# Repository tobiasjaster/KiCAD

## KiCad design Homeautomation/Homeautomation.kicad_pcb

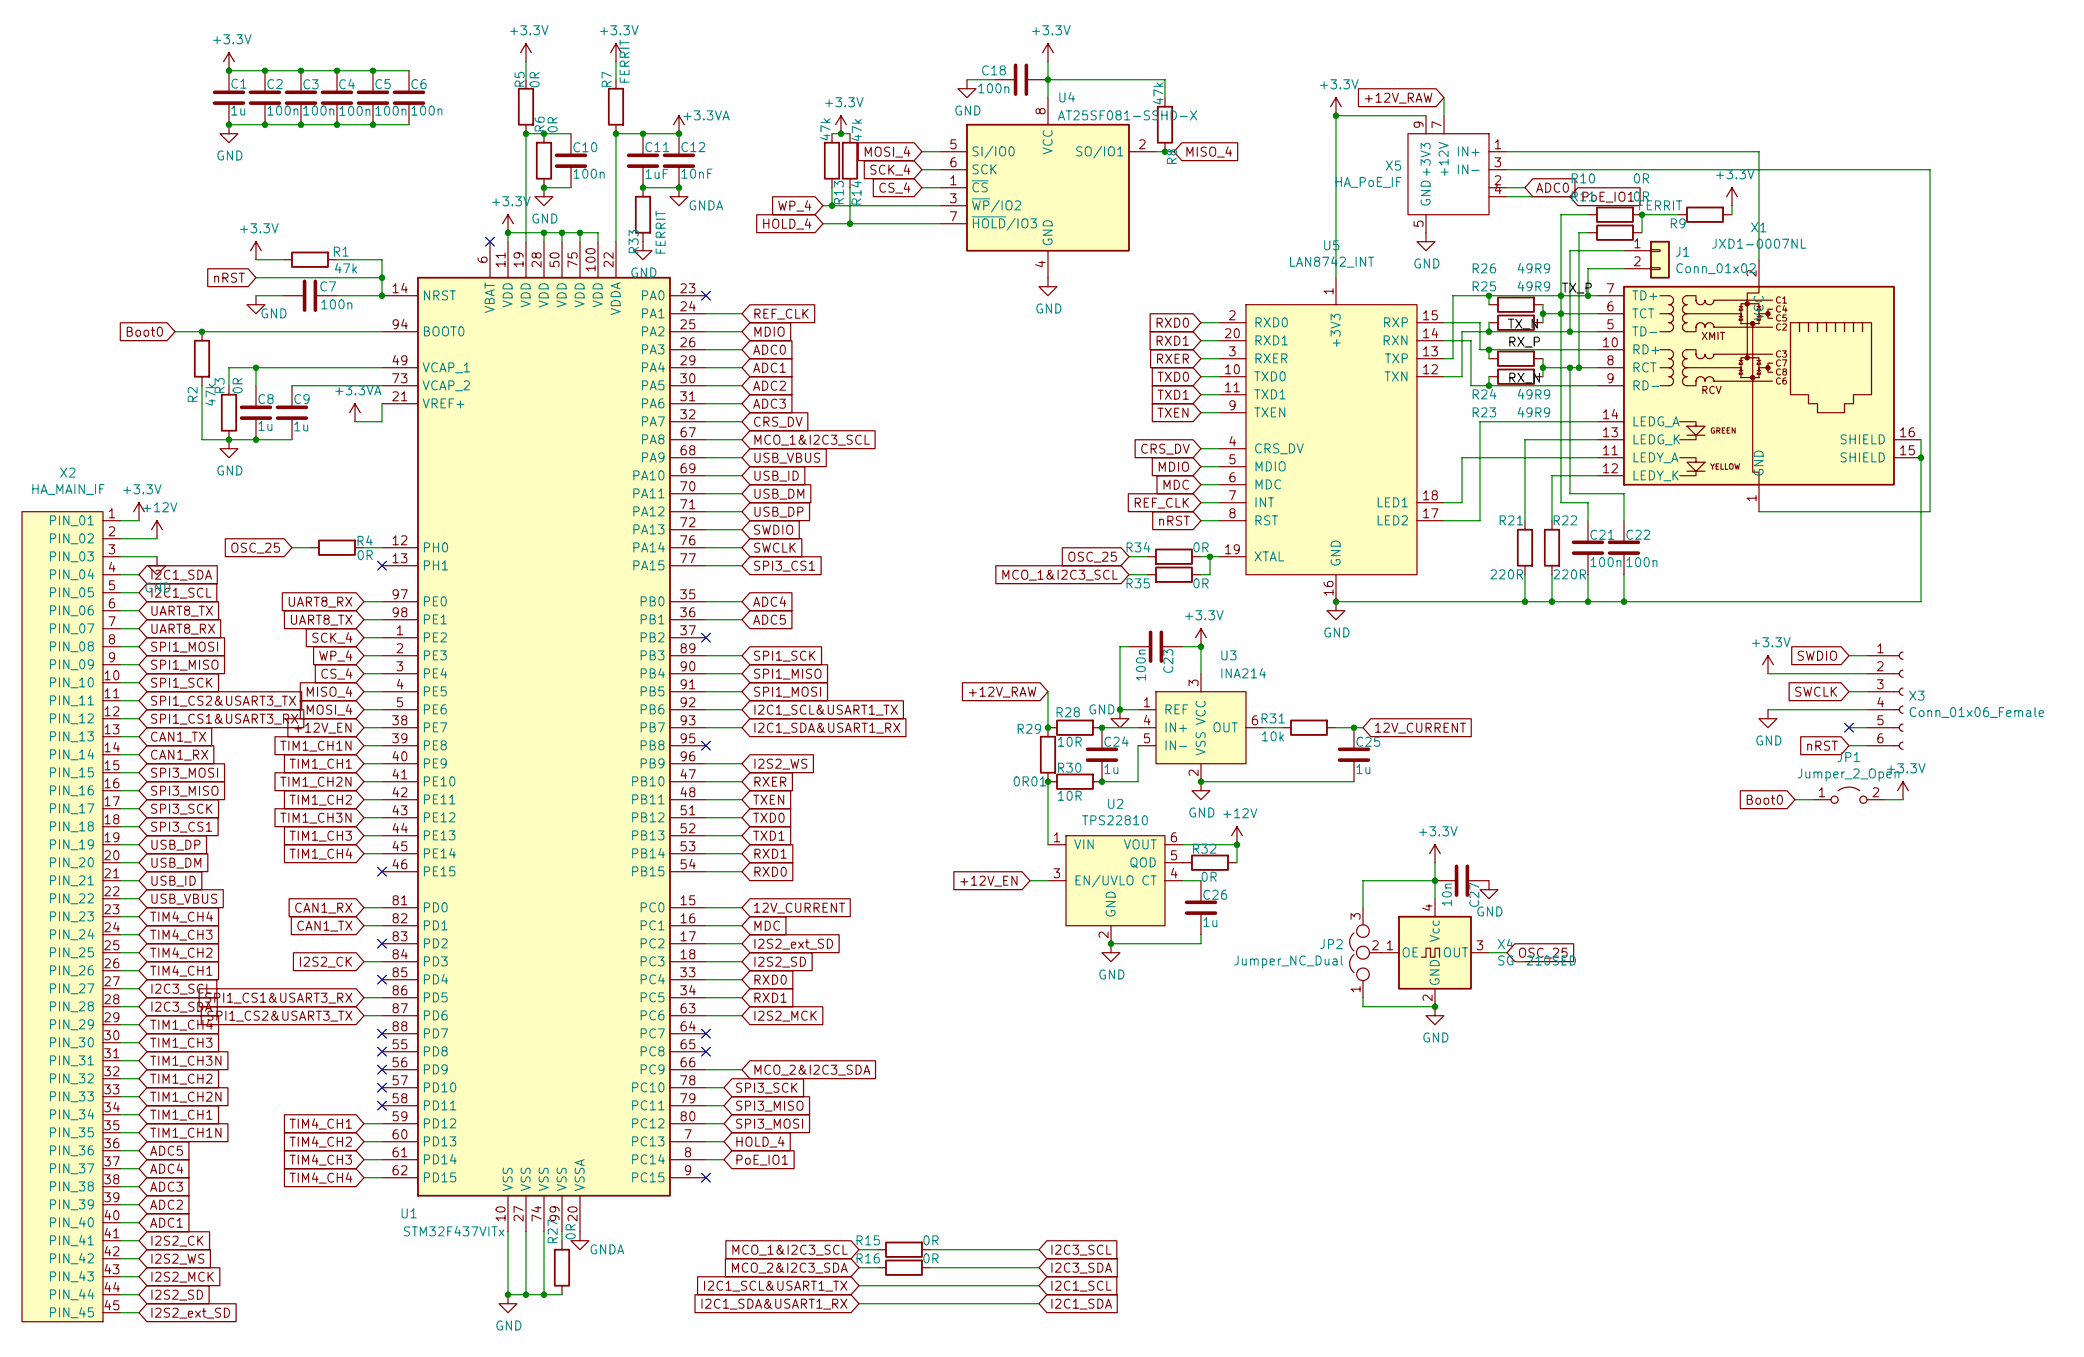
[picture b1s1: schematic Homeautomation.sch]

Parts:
C1, C8, C9, C24, C25, C26: 1u; C_0603_1608Metric
C2, C3, C4, C5, C6, C7, C10, C18, C21, C22, C23: 100n; C_0402_1005Metric
C11: 1uF; C_0603_1608Metric
C12: 10nF; C_0402_1005Metric
C27: 10n; C_0603_1608Metric
J1: Conn_01x02; Wago_243_211_1x02_P5.80mm_Vertical
JP1: Jumper_2_Open; SolderJumper-2_P1.3mm_Open_Pad1.0x1.5mm
JP2: Jumper_NC_Dual; SolderJumper-3_P1.3mm_Open_RoundedPad1.0x1.5mm
R1, R2, R8, R13, R14: 47k; R_0402_1005Metric
R3, R4, R5, R6, R10, R11, R15, R16, R27, R32, R34, R35: 0R; R_0402_1005Metric
R7, R9, R33: FERRIT; R_0603_1608Metric
R21, R22: 220R; R_0402_1005Metric
R23, R24, R25, R26: 49R9; R_0402_1005Metric
R28, R30: 10R; R_0402_1005Metric
R29: 0R01; R_0805_2012Metric
R31: 10k; R_0402_1005Metric
U1: STM32F437VITx; LQFP-100_14x14mm_P0.5mm
U2: TPS22810; SOT-23-6
U3: INA214; SOT-363_SC-70-6
U4: AT25SF081-SSHD-X; SOIC-8_3.9x4.9mm_P1.27mm
U5: LAN8742_INT; Bus_Interface_TJHome_Base
X1: JXD1-0007NL
X2: HA_MAIN_IF; HA_MAIN_IF2
X3: Conn_01x06_Female; JST_SH_SM06B-SRSS-TB_1x06-1MP_P1.00mm_Horizontal
X4: SG-210SED; Oscillator_SMD_SeikoEpson_SG210-4Pin_2.5x2.0mm
X5: HA_PoE_IF

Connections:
12V_CURRENT: C25.2, R31.2, U1.15 (PC0)
+3.3VA: C11.1, C12.1, R7.2, U1.21 (VREF+), U1.22 (VDDA)
+3V3: C1.1, C2.1, C3.1, C4.1, C5.1, C6.1, C18.1, C23.2, C27.1, JP1.2 (B), JP2.3, R1.1, R5.1, R7.1, R8.2, R9.2, R13.2, R14.2, U1.11 (VDD), U1.28 (VDD), U1.50 (VDD), U1.75 (VDD), U1.100 (VDD), U3.3 (VCC), U4.8 (VCC), U5.1 (+3V3), X2.1 (PIN_01), X3.2, X4.4 (Vcc), X5.9 (+3V3), X5.10; also elsewhere on the board
+12V: R32.2, U2.6 (VOUT), X2.2 (PIN_02)
+12V_EN: U1.38 (PE7), U2.3 (EN/UVLO)
+12V_RAW: R28.1, R29.1, X5.7 (+12V), X5.8
/RX_N: R23.1, U5.14 (RXN), X1.9 (RD-)
/RX_P: R24.1, U5.15 (RXP), X1.10 (RD+)
/TX_N: J1.1, R25.1, U5.12 (TXN), X1.5 (TD-)
/TX_P: C21.2, J1.2, R10.1, R25.2, R26.1, R26.2, U5.13 (TXP), X1.6 (TCT), X1.7 (TD+)
ADC0: U1.26 (PA3), X5.2
ADC1: U1.29 (PA4), X2.40 (PIN_40)
ADC2: U1.30 (PA5), X2.39 (PIN_39)
ADC3: U1.31 (PA6), X2.38 (PIN_38)
ADC4: U1.35 (PB0), X2.37 (PIN_37)
ADC5: U1.36 (PB1), X2.36 (PIN_36)
Boot0: JP1.1 (A), R2.1, U1.94 (BOOT0)
CAN1_RX: U1.81 (PD0), X2.14 (PIN_14)
CAN1_TX: U1.82 (PD1), X2.13 (PIN_13)
CRS_DV: U1.32 (PA7), U5.4 (CRS_DV)
CS_4: U1.3 (PE4), U4.1 (~CS)
GND: C1.2, C2.2, C3.2, C4.2, C5.2, C6.2, C7.2, C8.2, C9.2, C10.2, C18.2, C21.1, C22.1, C23.1, C25.1, C26.1, C27.2, JP2.1, R2.2, R3.1, R6.1, R21.2, R22.2, R27.1, R33.2, U1.10 (VSS), U1.27 (VSS), U1.74 (VSS), U2.2 (GND), U3.1 (REF), U3.2 (VSS), U4.4 (GND), U5.16 (GND), X1.15 (SHIELD), X1.16 (SHIELD), X2.3 (PIN_03), X3.4, X4.2 (GND), X5.5 (GND), X5.6 (GND)
GNDA: C11.2, C12.2, R33.1, U1.20 (VSSA)
HOLD_4: R14.1, U1.7 (PC13), U4.7 (~HOLD~/IO3)
I2C1_SCL: U1.92 (PB6), X2.5 (PIN_05); also elsewhere on the board
I2C1_SDA: U1.93 (PB7), X2.4 (PIN_04); also elsewhere on the board
I2C3_SCL: R15.2, X2.27 (PIN_27); also elsewhere on the board
I2C3_SDA: R16.2, X2.28 (PIN_28); also elsewhere on the board
I2S2_CK: U1.84 (PD3), X2.41 (PIN_41)
I2S2_MCK: U1.63 (PC6), X2.43 (PIN_43)
I2S2_SD: U1.18 (PC3), X2.44 (PIN_44)
I2S2_WS: U1.96 (PB9), X2.42 (PIN_42)
I2S2_ext_SD: U1.17 (PC2), X2.45 (PIN_45)
MCO_1&I2C3_SCL: R15.1, R35.2, U1.67 (PA8)
MCO_2&I2C3_SDA: R16.1, U1.66 (PC9)
MDC: U1.16 (PC1), U5.6 (MDC)
MDIO: U1.25 (PA2), U5.5 (MDIO)
MISO_4: R8.1, U1.4 (PE5), U4.2 (SO/IO1)
MOSI_4: U1.5 (PE6), U4.5 (SI/IO0)
unnamed: C8.1, R3.2, U1.49 (VCAP_1)
unnamed: C9.1, U1.73 (VCAP_2)
unnamed: C10.1, R5.2, R6.2, U1.19 (VDD)
unnamed: C22.2, R11.1, R23.2, R24.2, X1.8 (RCT)
unnamed: C24.1, R30.2, U3.5 (IN-)
unnamed: C24.2, R28.2, U3.4 (IN+)
unnamed: C26.2, U2.4 (CT)
unnamed: JP2.2, X4.1 (OE)
unnamed: R4.2, U1.12 (PH0)
unnamed: R9.1, R10.2, R11.2
unnamed: R21.1, X1.13 (LEDG_K)
unnamed: R22.1, X1.12 (LEDY_K)
unnamed: R27.2, U1.99 (VSS)
unnamed: R29.2, R30.1, U2.1 (VIN)
unnamed: R31.1, U3.6 (OUT)
unnamed: R32.1, U2.5 (QOD)
unnamed: R34.1, R35.1, U5.19 (XTAL)
unnamed: U5.17 (LED2), X1.14 (LEDG_A)
unnamed: U5.18 (LED1), X1.11 (LEDY_A)
unnamed: X1.1 (GND), X5.3 (IN-)
unnamed: X1.2 (VCC), X5.1 (IN+)
OSC_25: R4.1, R34.2, X4.3 (OUT)
PoE_IO1: U1.8 (PC14), X5.4
REF_CLK: U1.24 (PA1), U5.7 (INT)
RXD0: U1.33 (PC4), U1.54 (PB15), U5.2 (RXD0)
RXD1: U1.34 (PC5), U1.53 (PB14), U5.20 (RXD1)
RXER: U1.47 (PB10), U5.3 (RXER)
SCK_4: U1.1 (PE2), U4.6 (SCK)
SPI1_CS1&USART3_RX: U1.86 (PD5), X2.12 (PIN_12)
SPI1_CS2&USART3_TX: U1.87 (PD6), X2.11 (PIN_11)
SPI1_MISO: U1.90 (PB4), X2.9 (PIN_09)
SPI1_MOSI: U1.91 (PB5), X2.8 (PIN_08)
SPI1_SCK: U1.89 (PB3), X2.10 (PIN_10)
SPI3_CS1: U1.77 (PA15), X2.18 (PIN_18)
SPI3_MISO: U1.79 (PC11), X2.16 (PIN_16)
SPI3_MOSI: U1.80 (PC12), X2.15 (PIN_15)
SPI3_SCK: U1.78 (PC10), X2.17 (PIN_17)
SWCLK: U1.76 (PA14), X3.3
SWDIO: U1.72 (PA13), X3.1
TIM1_CH1: U1.40 (PE9), X2.34 (PIN_34)
TIM1_CH1N: U1.39 (PE8), X2.35 (PIN_35)
TIM1_CH2: U1.42 (PE11), X2.32 (PIN_32)
TIM1_CH2N: U1.41 (PE10), X2.33 (PIN_33)
TIM1_CH3: U1.44 (PE13), X2.30 (PIN_30)
TIM1_CH3N: U1.43 (PE12), X2.31 (PIN_31)
TIM1_CH4: U1.45 (PE14), X2.29 (PIN_29)
TIM4_CH1: U1.59 (PD12), X2.26 (PIN_26)
TIM4_CH2: U1.60 (PD13), X2.25 (PIN_25)
TIM4_CH3: U1.61 (PD14), X2.24 (PIN_24)
TIM4_CH4: U1.62 (PD15), X2.23 (PIN_23)
TXD0: U1.51 (PB12), U5.10 (TXD0)
TXD1: U1.52 (PB13), U5.11 (TXD1)
TXEN: U1.48 (PB11), U5.9 (TXEN)
UART8_RX: U1.97 (PE0), X2.7 (PIN_07)
UART8_TX: U1.98 (PE1), X2.6 (PIN_06)
USB_DM: U1.70 (PA11), X2.20 (PIN_20)
USB_DP: U1.71 (PA12), X2.19 (PIN_19)
USB_ID: U1.69 (PA10), X2.21 (PIN_21)
USB_VBUS: U1.68 (PA9), X2.22 (PIN_22)
WP_4: R13.1, U1.2 (PE3), U4.3 (~WP~/IO2)
nRST: C7.1, R1.2, U1.14 (NRST), U5.8 (RST), X3.6

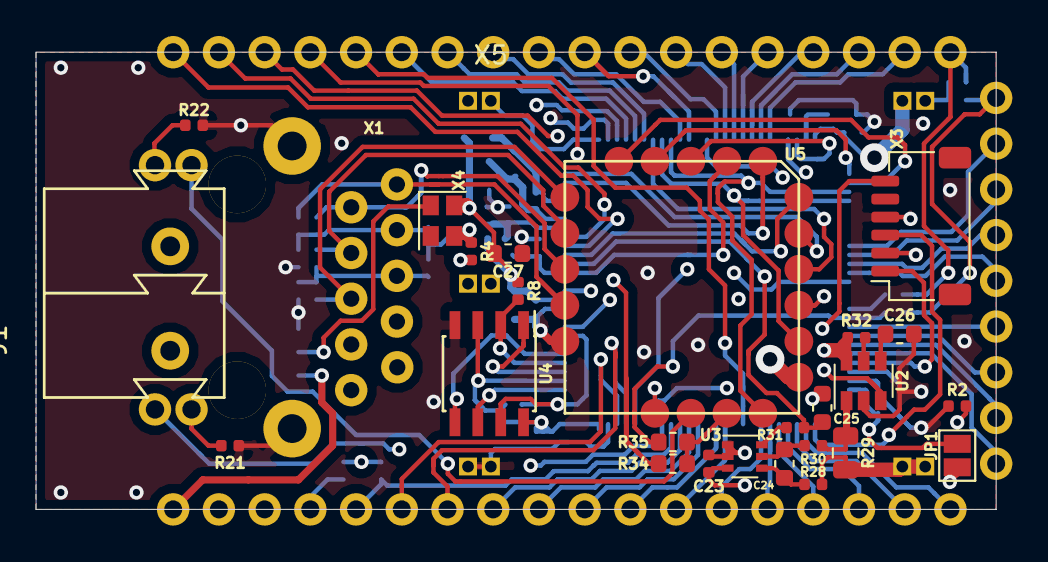
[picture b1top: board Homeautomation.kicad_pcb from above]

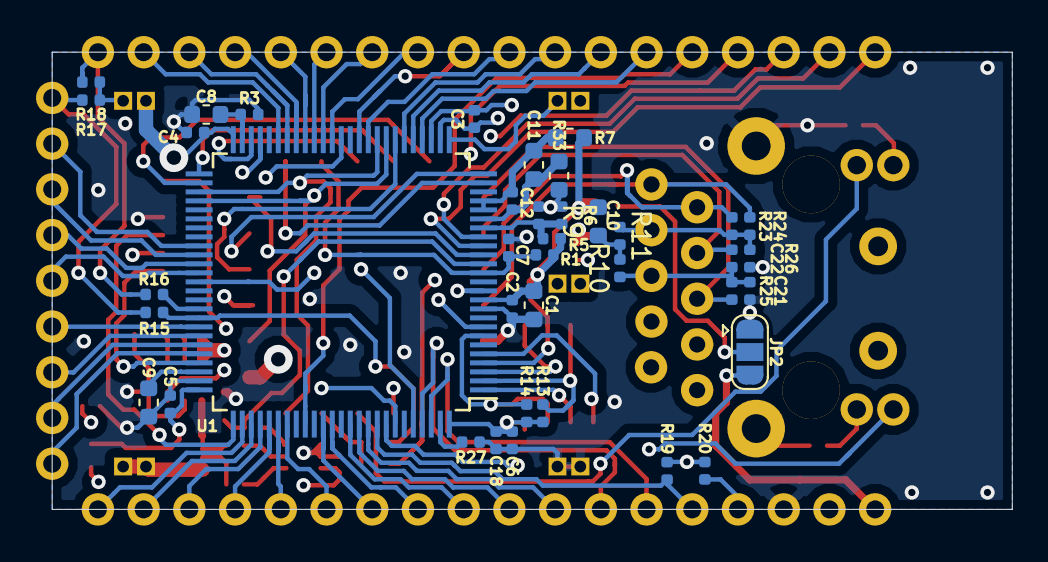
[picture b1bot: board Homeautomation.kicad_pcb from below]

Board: 4 copper layers, 53.3 x 25.4 mm, 67 parts (39 on the bottom side), 100 nets.

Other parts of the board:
R17, R18, R19, R20: 4k7; R_0402_1005Metric

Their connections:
+3V3: R17.2, R18.2, R19.2, R20.2; also elsewhere on the board
I2C1_SCL: R19.1; also elsewhere on the board
I2C1_SDA: R20.1; also elsewhere on the board
I2C3_SCL: R17.1; also elsewhere on the board
I2C3_SDA: R18.1; also elsewhere on the board

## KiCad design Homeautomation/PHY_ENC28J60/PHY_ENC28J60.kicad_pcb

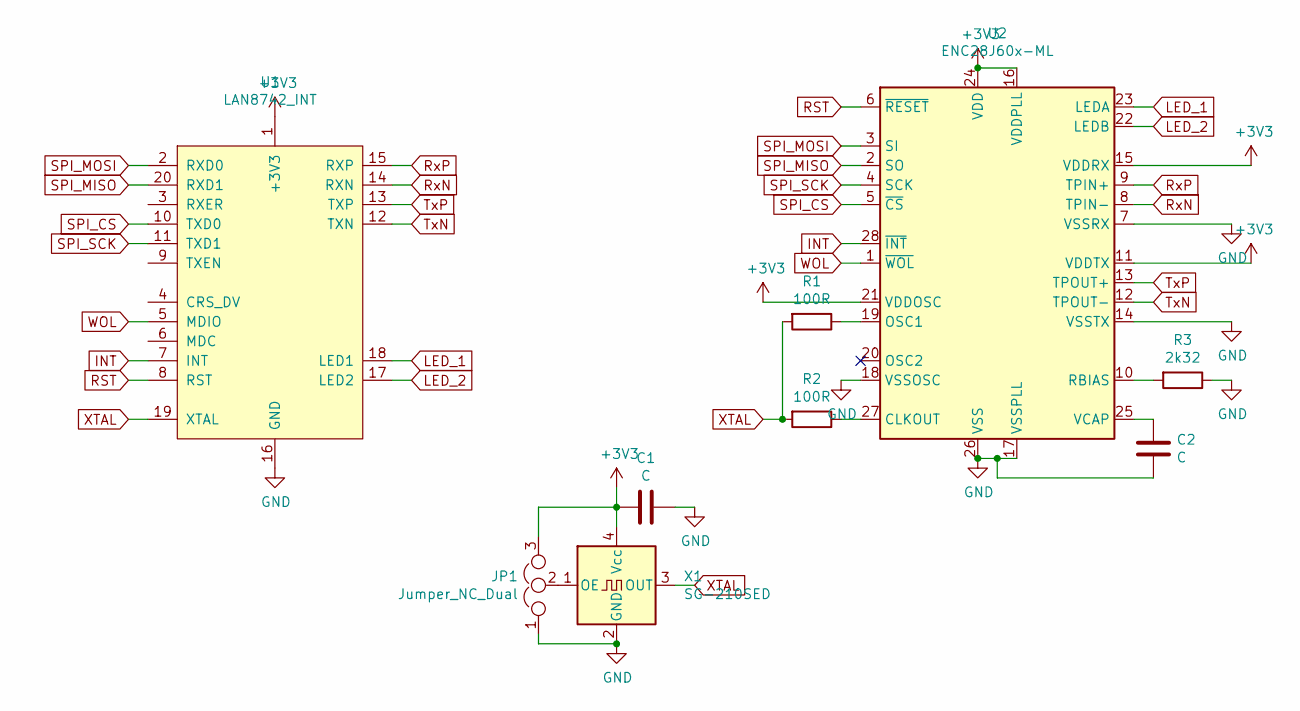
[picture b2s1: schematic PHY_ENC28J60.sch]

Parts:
C1: C; C_1206_3216Metric_Pad1.42x1.75mm_HandSolder
C2: C; C_0603_1608Metric_Pad1.05x0.95mm_HandSolder
JP1: Jumper_NC_Dual; SolderJumper-3_P0.7mm_Open_Pad0.5x0.8mm
R1, R2: 100R; R_0402_1005Metric
R3: 2k32; R_0603_1608Metric
U1: LAN8742_INT; LAN8742_INT_B
U2: ENC28J60x-ML; QFN-28-1EP_6x6mm_P0.65mm_EP4.25x4.25mm
X1: SG-210SED; Oscillator_SMD_SeikoEpson_SG210-4Pin_2.5x2.0mm

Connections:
+3V3: C1.2, JP1.3, U1.1 (+3V3), U2.11 (VDDTX), U2.15 (VDDRX), U2.16 (VDDPLL), U2.21 (VDDOSC), U2.24 (VDD), X1.4 (Vcc)
GND: C1.1, C2.2, JP1.1, R3.1, U1.16 (GND), U2.7 (VSSRX), U2.14 (VSSTX), U2.17 (VSSPLL), U2.18 (VSSOSC), U2.26 (VSS), X1.2 (GND)
INT: U1.7 (INT), U2.28 (~INT)
LED_1: U1.18 (LED1), U2.23 (LEDA)
LED_2: U1.17 (LED2), U2.22 (LEDB)
unnamed: C2.1, U2.25 (VCAP)
unnamed: JP1.2, X1.1 (OE)
unnamed: R1.1, U2.19 (OSC1)
unnamed: R2.1, U2.27 (CLKOUT)
unnamed: R3.2, U2.10 (RBIAS)
RST: U1.8 (RST), U2.6 (~RESET)
RxN: U1.14 (RXN), U2.8 (TPIN-)
RxP: U1.15 (RXP), U2.9 (TPIN+)
SPI_CS: U1.10 (TXD0), U2.5 (~CS)
SPI_MISO: U1.20 (RXD1), U2.2 (SO)
SPI_MOSI: U1.2 (RXD0), U2.3 (SI)
SPI_SCK: U1.11 (TXD1), U2.4 (SCK)
TxN: U1.12 (TXN), U2.12 (TPOUT-)
TxP: U1.13 (TXP), U2.13 (TPOUT+)
WOL: U1.5 (MDIO), U2.1 (~WOL)
XTAL: R1.2, R2.2, U1.19 (XTAL), X1.3 (OUT)

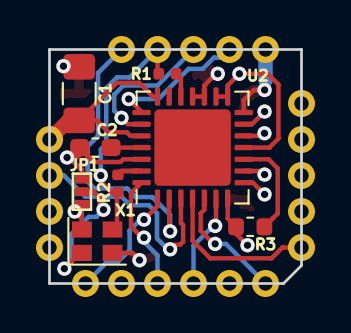
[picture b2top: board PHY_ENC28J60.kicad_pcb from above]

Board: 4 copper layers, 14.0 x 13.0 mm, 9 parts (0 on the bottom side), 21 nets.

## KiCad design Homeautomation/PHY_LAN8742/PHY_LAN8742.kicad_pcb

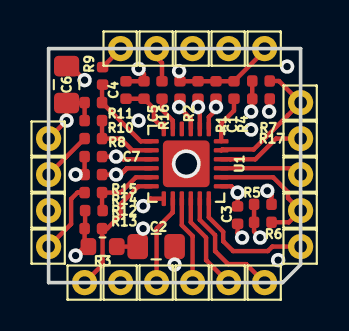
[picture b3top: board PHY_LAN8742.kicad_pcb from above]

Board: 4 copper layers, 14.0 x 13.0 mm, 45 parts (0 on the bottom side), 27 nets.

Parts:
C1, C3, C5, C7: 100n; C_0402_1005Metric
C2, C6: 10u; C_0805_2012Metric_Pad1.15x1.40mm_HandSolder
C4: 470p; C_0402_1005Metric
R1, R2: 10k; R_0402_1005Metric
R3: FERRIT; R_0603_1608Metric
R4: 12k1; R_0402_1005Metric
R5, R6, R7, R17: 50; R_0402_1005Metric
R8, R9, R14: 33; R_0402_1005Metric
R10, R11, R12, R13, R15: 4k7; R_0402_1005Metric
R16: 100; R_0402_1005Metric
TP1, TP2, TP3, TP4, TP5, TP6, TP7, TP8, TP9, TP10, TP11, TP12, TP13, TP14, TP15, TP16, TP17, TP18, TP19, TP20: TestPoint; Pin_D0.7mm_L6.5mm_W1.8mm_FlatFork
U1: LAN8742A; QFN-24-1EP_4x4mm_P0.5mm_EP2.6x2.6mm

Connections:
+1V2: C4.1, C5.1, U1.6
+3.3VA: C1.1, C2.1, C3.1, R3.2, U1.1, U1.19
+3V3: C6.1, C7.1, R3.1, R5.1, R6.1, R7.1, R10.1, R11.1, R12.1, R13.1, R17.1, TP16.1, U1.9
/CRS_DV: R12.2, R14.2, U1.11
/INT: TP11.7, U1.14
/LED1: R2.1, TP19.18, U1.3
/LED2: R1.1, TP20.17, U1.2
/MDC: TP9.6, U1.13
/MDIO: R13.2, TP8.5, U1.12
/RBIAS: R4.2, U1.24
/RST: TP10.8, U1.15
/RXD0: R8.2, R10.2, U1.8
/RXD1: R9.2, R11.2, U1.7
/RXER: R15.1, TP6.3, U1.10
/RXN: R17.2, TP12.14, U1.22
/RXP: R7.2, TP13.15, U1.23
/TXD1: TP2.11, U1.18
/TXDO: TP1.10, U1.17
/TXEN: TP3.9, U1.16
/TXN: R6.2, TP14.12, U1.20
/TXP: R5.2, TP15.13, U1.21
/XTAL1: R16.2, U1.5
GND: C1.2, C2.2, C3.2, C4.2, C5.2, C6.2, C7.2, R1.2, R2.2, R4.1, R15.2, TP17.16, U1.25
unnamed: R8.1, TP4.2
unnamed: R9.1, TP5.20
unnamed: R14.1, TP7.4
unnamed: R16.1, TP18.19

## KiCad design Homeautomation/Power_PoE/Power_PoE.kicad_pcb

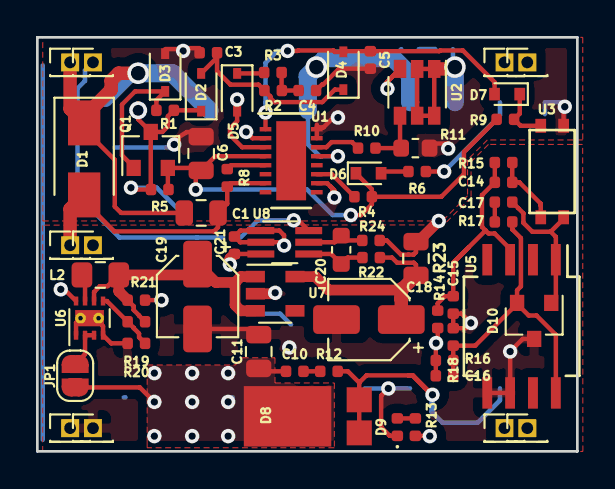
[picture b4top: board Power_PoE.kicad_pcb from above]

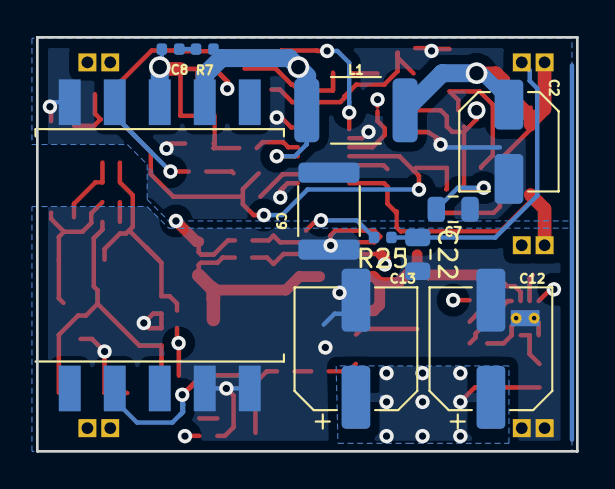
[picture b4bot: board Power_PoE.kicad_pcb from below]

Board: 4 copper layers, 30.0 x 23.0 mm, 79 parts (11 on the bottom side), 41 nets.

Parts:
C1: 100nF; C_0805_2012Metric
C2: 4.7uF; C_Elec_5x5.8
C3: 470nF; C_0402_1005Metric
C4, C14, C15: 10nF; C_0402_1005Metric
C5, C8: C; C_0402_1005Metric
C6: 4.7uF; C_0805_2012Metric
C7: 1uF; C_0805_2012Metric
C9: 2.2nF; C_1812_4532Metric
C10: 680pF; C_0402_1005Metric
C11: 10uF; C_0805_2012Metric
C12, C13: 47uF; CP_Elec_6.3x7.7
C16: R; C_0402_1005Metric
C17: 33nF; C_0402_1005Metric
C18, C19: 10uF; CP_Elec_4x5.8
C20: 1u; C_0603_1608Metric
C21: 100n; C_0402_1005Metric
C22: 1u; C_0805_2012Metric
D1: SMAJ58A-13-F; D_SMA
D2, D4, D5: 1N4148WS-7-F; D_SOD-323
D3: D_Schottky; D_SOD-323
D6, D7: BAS516; D_SOD-523
D8: PDS360-13; PDS360
D9: LED; LED_0402_1005Metric
D10: TL431DBZ; SOT-23
JP1: SolderJumper_2_Open; SolderJumper-2_P1.3mm_Open_RoundedPad1.0x1.5mm
L1: DO1608C-822ML; DO1608
L2: DO1608C-822ML; L_0805_2012Metric_Pad1.15x1.40mm_HandSolder
Q1: MMBTA42LT1G; SOT-23
R1, R5: 220k; R_0402_1005Metric
R2: 300k; R_0402_1005Metric
R3: 100R; R_0402_1005Metric
R4: 200k; R_0402_1005Metric
R6: 150R; R_0402_1005Metric
R7: R; R_0402_1005Metric
R8: 45R3; R_0402_1005Metric
R9: 6k8; R_0402_1005Metric
R10, R19, R20, R21, R25: 10k; R_0402_1005Metric
R11: 0R05; R_0603_1608Metric
R12: 13R; R_0402_1005Metric
R13: 2k; R_0402_1005Metric
R14: 1k; R_0402_1005Metric
R15: 7k5; R_0402_1005Metric
R16: 107k; R_0402_1005Metric
R17: 61k9; R_0402_1005Metric
R18: 28k; R_0402_1005Metric
R22, R24: 10R; R_0402_1005Metric
R23: 0R01; R_0805_2012Metric
TP1, TP2, TP3, TP4, TP5, TP6, TP7, TP8, TP9, TP10: TestPoint; PinHeader_1x01_P1.27mm_Vertical
U1: LTC4267-DHC; DFN-16-1EP_3x5mm_P0.5mm_EP1.66x4.4mm
U2: FDC2612; SuperSOT-6
U3: PS2911-1
U4: PA1138NL; Pulse_PA1138
U5: LT1431; SO-8_5.3x6.2mm_P1.27mm
U6: TPS62125DSG; WSON-8-1EP_2x2mm_P0.5mm_EP0.9x1.6mm_ThermalVias
U7: MIC5504-3.3YM5; SOT-23-5
U8: INA21X; SOT-363_SC-70-6_Handsoldering

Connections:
+3V3: C21.1, R23.1, R24.2, TP7.1, TP8.1, U8.3
+12V: C10.1, C11.1, C12.1, C13.1, C16.1, D8.1, JP1.1, R13.1, R14.2, R16.2, TP3.1, TP5.1
Earth: C2.2, C3.2, C4.2, C5.2, C6.2, C7.2, C9.2, D3.2, R11.2, U1.2, U1.10, U1.15, U1.16, U3.3, U4.1
GND: C9.1, C11.2, C12.2, C13.2, C15.2, C18.2, C19.2, C21.2, C22.2, D9.1, D10.3, R18.1, R20.2, TP4.1, TP6.1, U4.9, U4.10, U5.5, U5.6, U6.1, U6.4, U6.9, U7.2, U8.1, U8.2
unnamed: C1.1, C2.1, D1.1, L1.1, TP1.1
unnamed: C1.2, D1.2, R8.2, TP2.1, U1.7
unnamed: C3.1, D2.2, D4.1, R2.1
unnamed: C4.1, R2.2, R3.1
unnamed: C5.1, D4.2, D7.2, U1.1
unnamed: C6.1, D6.1, Q1.2, R4.2, R5.2, R9.2, U1.4
unnamed: C7.1, D2.1, L1.2, Q1.3, R1.1, R5.1, R7.1, U1.13, U4.4
unnamed: C8.1, R7.2
unnamed: C8.2, U2.1, U2.2, U2.5, U2.6, U4.3
unnamed: C10.2, R12.2
unnamed: C14.1, C15.1, R14.1, R15.2, U5.3
unnamed: C14.2, R15.1, U3.1
unnamed: C16.2, D10.2, R16.1, R17.1, R18.2, U5.8
unnamed: C17.1, D10.1, U3.2, U5.1
unnamed: C17.2, R17.2
unnamed: C18.1, R22.2, R23.2, U7.5
unnamed: C19.1, L2.2, R19.1, R21.1, U6.6, U7.1, U7.3
unnamed: C20.1, R24.1, U8.5
unnamed: C20.2, R22.1, U8.4
unnamed: C22.1, R25.1, TP10.1
unnamed: D3.1, Q1.1, R1.2
unnamed: D5.1, R3.2
unnamed: D5.2, U1.3, U2.3
unnamed: D6.2, R6.1
unnamed: D7.1, R9.1, U3.4
unnamed: D8.2, R12.1, U4.7
unnamed: D9.2, R13.2
unnamed: JP1.2, U6.2, U6.3
unnamed: L2.1, U6.7
unnamed: R4.1, U1.11
unnamed: R6.2, U4.2
unnamed: R8.1, U1.5
unnamed: R10.1, R11.1, U2.4
unnamed: R10.2, U1.14
unnamed: R19.2, R20.1, U6.5
unnamed: R21.2, U6.8
unnamed: R25.2, U8.6

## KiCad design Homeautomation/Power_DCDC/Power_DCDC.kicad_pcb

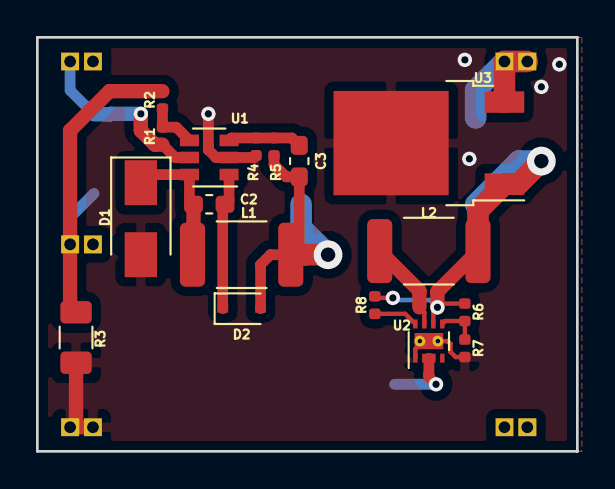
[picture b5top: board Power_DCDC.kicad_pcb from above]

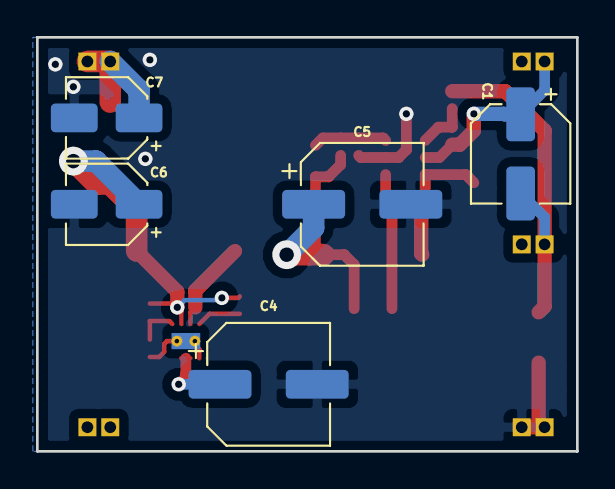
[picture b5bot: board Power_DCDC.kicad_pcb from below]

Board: 4 copper layers, 30.0 x 23.0 mm, 23 parts (5 on the bottom side), 13 nets.

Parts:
C1: CP; CP_Elec_5x5.8
C2, C3: C; C_0603_1608Metric_Pad1.05x0.95mm_HandSolder
C4, C5: CP; CP_Elec_6.3x7.7
C6, C7: CP; CP_Elec_4x5.8
D1: D_Schottky; D_SMA
D2: 1N4148WS; D_SOD-323
L1, L2: L; DO1608
R1, R2, R4, R5, R6, R7, R8: R; R_0402_1005Metric
R3: R; R_1206_3216Metric
U1: MCP16331CH; SOT-23-6
U2: TPS62125DSG; WSON-8-1EP_2x2mm_P0.5mm_EP0.9x1.6mm_ThermalVias
U3: LF120_TO252; TO-252-2
X1: HA_PoE_IF

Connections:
+3V3: C7.1, U3.3, X1.9, X1.10
+12V: C3.1, C4.1, C5.1, D2.2, L1.2, R5.1, U2.2, U2.3, X1.7, X1.8
GND: C4.2, C5.2, C6.2, C7.2, D1.2, R3.1, R4.1, R7.1, U1.2, U2.1, U2.9, U3.2, X1.5, X1.6
unnamed: C1.2, R2.2, R3.2, X1.3
unnamed: C2.1, D1.1, L1.1, U1.6
unnamed: C2.2, D2.1, U1.1
unnamed: C3.2, R4.2, R5.2, U1.3
unnamed: C6.1, L2.2, R6.2, R8.2, U2.6, U3.1
unnamed: L2.1, U2.7
unnamed: R1.1, R2.1, U1.4
unnamed: R6.1, R7.2, U2.5
unnamed: R8.1, U2.8
VCC: C1.1, R1.2, U1.5, X1.1

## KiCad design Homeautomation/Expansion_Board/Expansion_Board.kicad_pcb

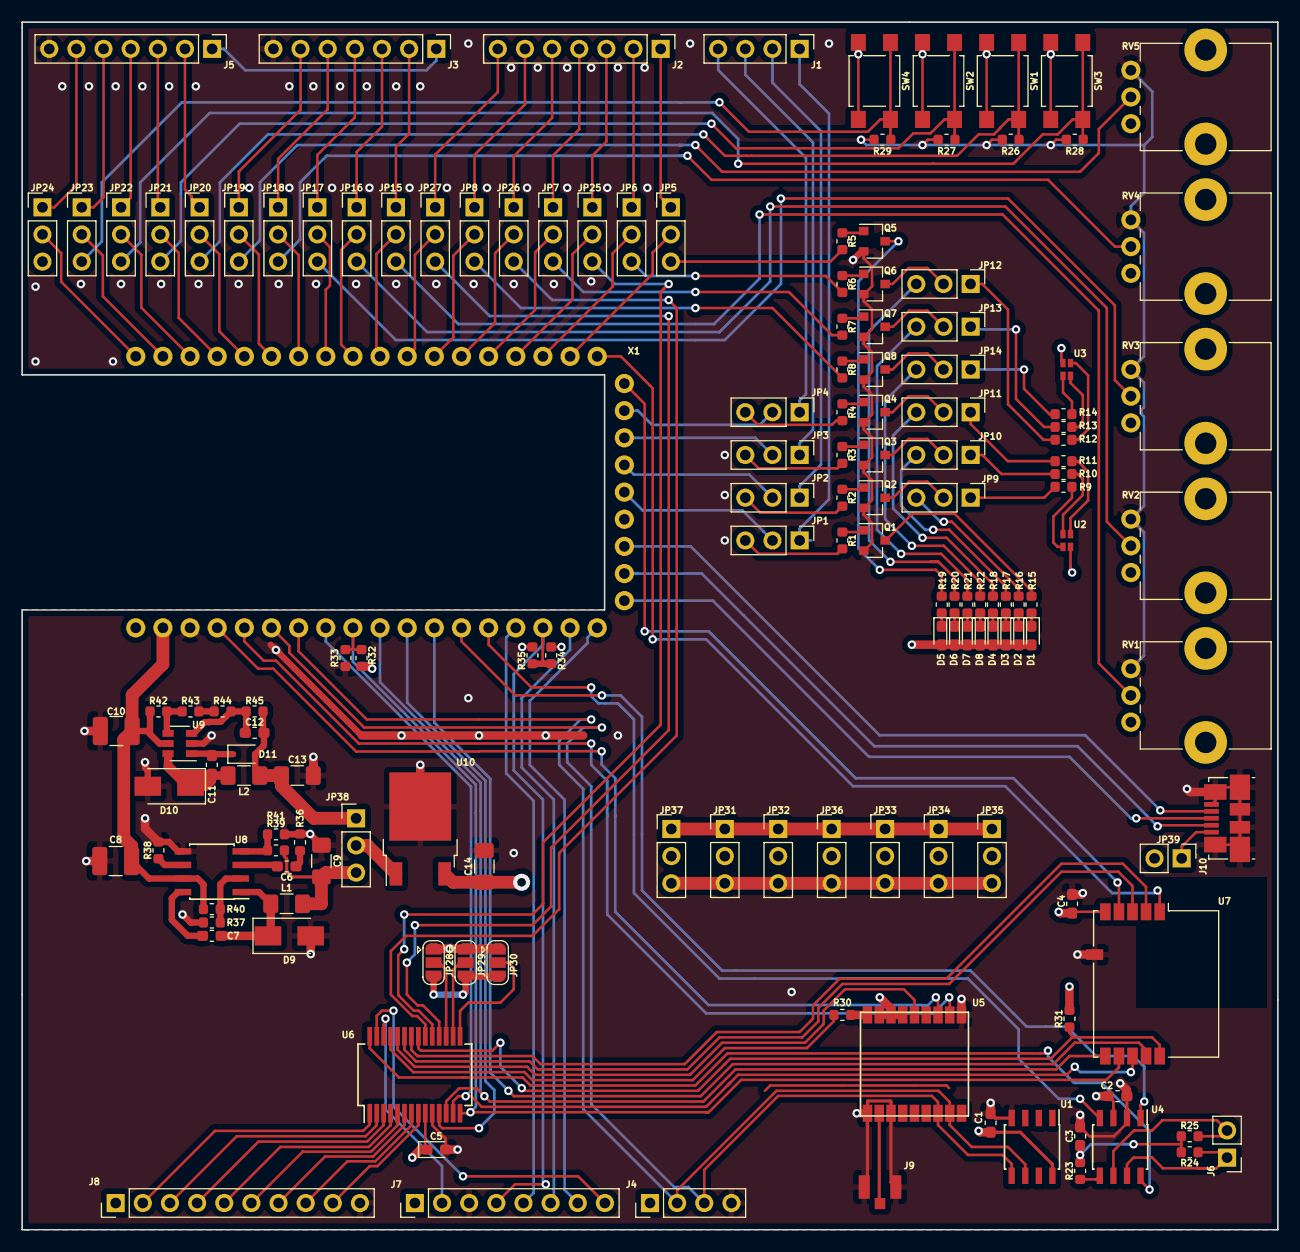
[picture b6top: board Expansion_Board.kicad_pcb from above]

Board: 4 copper layers, 117.5 x 113.0 mm, 149 parts (0 on the bottom side), 175 nets.

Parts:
C1, C2, C3, C4: C; C_0603_1608Metric_Pad1.05x0.95mm_HandSolder
C5: C; LED_0603_1608Metric_Pad1.05x0.95mm_HandSolder
C6: 330pF; C_0603_1608Metric_Pad1.05x0.95mm_HandSolder
C7, C11: 100n; C_0603_1608Metric_Pad1.05x0.95mm_HandSolder
C8, C10: 4.7uF; C_1210_3225Metric_Pad1.42x2.65mm_HandSolder
C9, C13, C14: 33uF; C_1206_3216Metric_Pad1.42x1.75mm_HandSolder
C12: 20pF; C_0603_1608Metric_Pad1.05x0.95mm_HandSolder
D1, D2, D3, D4, D5, D6, D7, D8: LED; LED_0603_1608Metric_Pad1.05x0.95mm_HandSolder
D9, D10: D_Schottky; D_SMA
D11: 1N4148WS; D_SOD-323
J1, J4: Conn_01x04; PinHeader_1x04_P2.54mm_Vertical
J2, J3, J5: Conn_01x07; PinHeader_1x07_P2.54mm_Vertical
J6: Conn_01x02; PinHeader_1x02_P2.54mm_Vertical
J7: Conn_01x08; PinHeader_1x08_P2.54mm_Vertical
J8: Conn_01x10; PinHeader_1x10_P2.54mm_Vertical
J9: Conn_01x03_Male; CONUFL001-SMD
J10: USB_OTG; USB_Micro-B_Molex_47346-0001
JP1, JP2, JP3, JP4, JP5, JP6, JP7, JP8, JP9, JP10, JP11, JP12, JP13, JP14, JP15, JP16, JP17, JP18, JP19, JP20, JP21, JP22, JP23, JP24, JP25, JP26, JP27, JP31, JP32, JP33, JP34, JP35, JP36, JP37, JP38: Jumper_NC_Dual; PinHeader_1x03_P2.54mm_Vertical
JP28, JP29, JP30: SolderJumper_3_Open; SolderJumper-3_P1.3mm_Open_RoundedPad1.0x1.5mm
JP39: Jumper_2_Open; PinHeader_1x02_P2.54mm_Vertical
L1, L2: L; L_1206_3216Metric_Pad1.42x1.75mm_HandSolder
Q1, Q2, Q3, Q4, Q5, Q6, Q7, Q8: BC847; SOT-23
R1, R2, R3, R4, R5, R6, R7, R8, R9, R10, R11, R12, R13, R14, R15, R16, R17, R18, R19, R20, R21, R22, R23, R24, R25, R26, R27, R28, R29, R30, R31, R32, R33, R34, R35: R; R_0603_1608Metric
R36: 47k5; R_0603_1608Metric
R37, R43: 17k4; R_0603_1608Metric
R38: 200k; R_0603_1608Metric
R39: 40k2; R_0603_1608Metric
R40, R42: 100k; R_0603_1608Metric
R41: 210k; R_0603_1608Metric
R44: 10k; R_0603_1608Metric
R45: 52k3; R_0603_1608Metric
RV1, RV2, RV3, RV4, RV5: R_POT; Potentiometer_Alps_RK09K_Single_Vertical
SW1, SW2, SW3, SW4: SW_Push; SW_SPST_TL3305A
U1: ATECC608A-SSHDA; SOIC-8_3.9x4.9mm_P1.27mm
U2, U3: LED_RGBA; 150066M153000
U4: MCP2561-E-SN; SOIC-8_3.9x4.9mm_P1.27mm
U5: TESEO-LIV3F; Teseo-LIV3F
U6: MCP23S17_SS; SSOP-28_5.3x10.2mm_P0.65mm
U7: SPBTLE-RF0; ST_SPBTLE
U8: MP4559; SOIC-8_3.9x4.9mm_P1.27mm
U9: MCP16331CH; SOT-23-6
U10: AP7363-33D; TO-252-2
X1: HA_MAIN_IF; HA_MAIN_IF2

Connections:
+3.3VP: C14.1, JP31.3, JP32.3, JP33.3, JP34.3, JP35.3, JP36.3, JP37.3, U10.3
+3V3: J8.1, JP31.1, JP32.1, JP33.1, JP34.1, JP35.1, JP36.1, JP37.1, R32.2, R34.2, X1.1
+5V: JP38.2, JP39.2, U10.1
+12V: C8.2, C10.2, R40.2, R42.1, U8.7, U9.5, X1.2
ADC1: JP19.2, X1.40
ADC1_OUT: J3.6, JP19.1
ADC2: JP18.2, X1.39
ADC2_OUT: J3.5, JP18.1
ADC3: JP17.2, X1.38
ADC3_OUT: J3.4, JP17.1
ADC4: JP16.2, X1.37
ADC4_OUT: J3.3, JP16.1
ADC5: JP15.2, X1.36
ADC5_OUT: J3.2, JP15.1
CAN1_RX: U4.4, X1.14
CAN1_TX: U4.1, X1.13
GND: C1.2, C2.2, C3.1, C4.2, C5.2, C8.1, C9.2, C10.1, C13.2, C14.2, D9.2, D10.2, J3.7, J4.4, J5.7, J7.3, J8.10, J9.1, J9.2, J10.5, J10.6, JP28.1, JP29.1, JP30.1, Q1.2, Q2.2, Q3.2, Q4.2, Q5.2, Q6.2, Q7.2, Q8.2, R26.1, R27.1, R28.1, R29.1, R33.1, R35.1, R36.1, R37.1, R38.1, R39.1, R43.1, R44.1, RV1.3, RV2.3, RV3.3, RV4.3, RV5.3, U1.4, U4.2, U5.1, U5.10, U5.12, U6.10, U7.6, U8.5, U9.2, U10.2, X1.3
GPIO_EXP_0: R31.1, U6.21, U7.11
GPIO_EXP_1: U6.22, U7.2
GPIO_EXP_2: U6.23, U7.3
GPIO_EXP_3: U5.5, U6.24
GPIO_EXP_4: R30.1, U6.25
GPIO_EXP_5: J7.2, U6.26
GPIO_EXP_6: J7.8, U6.27
GPIO_EXP_7: U4.8, U6.28
I2C1_SCL: J4.2, U1.6, U5.17, X1.7
I2C1_SDA: J4.3, U1.5, U5.16, X1.6
I2C3_SCL: U7.4, X1.27
I2C3_SDA: U7.1, X1.28
I2S2_CK: JP20.2, X1.41
I2S2_CK_OUT: J5.2, JP20.1
I2S2_MCK: JP22.2, X1.43
I2S2_MCK_OUT: J5.4, JP22.1
I2S2_SD: JP23.2, X1.44
I2S2_SD_OUT: J5.5, JP23.1
I2S2_WS: JP21.2, X1.42
I2S2_WS_OUT: J5.3, JP21.1
I2S2_ext_SD: JP24.2, X1.45
I2S2_ext_SD_OUT: J5.6, JP24.1
unnamed: C1.1, JP33.2, U1.8
unnamed: C2.1, JP34.2, U4.3
unnamed: C3.2, R23.1, R24.2, R25.1
unnamed: C4.1, JP35.2, R31.2, U7.5
unnamed: C5.1, JP28.3, JP29.3, JP30.3, JP37.2, U6.9
unnamed: C6.1, U8.3
unnamed: C6.2, R36.2
unnamed: C7.1, D9.1, L1.1, U8.1
unnamed: C7.2, U8.8
unnamed: C9.1, JP38.3, L1.2, R41.2
unnamed: C11.1, D10.1, L2.1, U9.6
unnamed: C11.2, D11.1, U9.1
unnamed: C12.1, C13.1, D11.2, JP38.1, L2.2, R45.2
unnamed: C12.2, R44.2, R45.1, U9.3
unnamed: D1.1, R15.1
unnamed: D1.2, D2.2, D3.2, D4.2, D5.2, D6.2, D7.2, D8.2, JP32.2, RV1.1, RV2.1, RV3.1, RV4.1, RV5.1, SW1.2, SW2.2, SW3.2, SW4.2, U2.1, U3.1
unnamed: D2.1, R16.1
unnamed: D3.1, R17.1
unnamed: D4.1, R18.1
unnamed: D5.1, R19.1
unnamed: D6.1, R20.1
unnamed: D7.1, R21.1
unnamed: D8.1, R22.1
unnamed: J3.1, J4.1, J5.1, J7.1, JP31.2
unnamed: J6.1, R24.1, U4.7
unnamed: J6.2, R25.2, U4.6
unnamed: J8.2, U6.1
unnamed: J8.3, U6.2
unnamed: J8.4, U6.3
unnamed: J8.5, U6.4
unnamed: J8.6, U6.5
unnamed: J8.7, U6.6
unnamed: J8.8, U6.7
unnamed: J8.9, U6.8
unnamed: J9.3, U5.11
unnamed: J10.1, JP39.1
unnamed: JP9.1, R9.2
unnamed: JP9.2, Q2.3
unnamed: JP9.3, R16.2
unnamed: JP10.1, R10.2
unnamed: JP10.2, Q3.3
unnamed: JP10.3, R17.2
unnamed: JP11.1, R11.2
unnamed: JP11.2, Q4.3
unnamed: JP11.3, R18.2
unnamed: JP12.1, R12.2
unnamed: JP12.2, Q6.3
unnamed: JP12.3, R20.2
unnamed: JP13.1, R13.2
unnamed: JP13.2, Q7.3
unnamed: JP13.3, R21.2
unnamed: JP14.1, R14.2
unnamed: JP14.2, Q8.3
unnamed: JP14.3, R22.2
unnamed: JP15.3, RV1.2
unnamed: JP16.3, RV2.2
unnamed: JP17.3, RV3.2
unnamed: JP18.3, RV4.2
unnamed: JP19.3, RV5.2
unnamed: JP20.3, R26.2, SW1.1
unnamed: JP21.3, R27.2, SW2.1
unnamed: JP22.3, R28.2, SW3.1
unnamed: JP23.3, R29.2, SW4.1
unnamed: JP25.3, U6.19
unnamed: JP26.3, U6.20
unnamed: JP27.3, U6.18
unnamed: JP28.2, U6.17
unnamed: JP29.2, U6.16
unnamed: JP30.2, U6.15
unnamed: JP36.2, U5.6, U5.7, U5.8
unnamed: Q1.1, R1.1
unnamed: Q1.3, R15.2
unnamed: Q2.1, R2.1
unnamed: Q3.1, R3.1
unnamed: Q4.1, R4.1
unnamed: Q5.1, R5.1
unnamed: Q5.3, R19.2
unnamed: Q6.1, R6.1
unnamed: Q7.1, R7.1
unnamed: Q8.1, R8.1
unnamed: R9.1, U2.2
unnamed: R10.1, U2.3
unnamed: R11.1, U2.4
unnamed: R12.1, U3.2
unnamed: R13.1, U3.3
unnamed: R14.1, U3.4
unnamed: R23.2, U4.5
unnamed: R30.2, U5.9
unnamed: R37.2, R40.1, U8.2
unnamed: R38.2, U8.6
unnamed: R39.2, R41.1, U8.4
unnamed: R42.2, R43.2, U9.4
SPI1_CS1: U6.11, X1.11
SPI1_CS2: U7.10, X1.12
SPI1_MISO: R32.1, R33.2, U6.14, U7.8, X1.9
SPI1_MOSI: U6.13, U7.9, X1.8
SPI1_SCK: U6.12, U7.7, X1.10
SPI3_CS1: J7.7, X1.18
SPI3_MISO: J7.4, R34.1, R35.2, X1.16
SPI3_MOSI: J7.5, X1.15
SPI3_SCK: J7.6, X1.17
TIM1_CH1: JP8.2, X1.34
TIM1_CH1N: JP27.2, X1.35
TIM1_CH1N_OUT: J2.7, JP27.1
TIM1_CH1_LED: JP8.3, R8.2
TIM1_CH1_OUT: J2.6, JP8.1
TIM1_CH2: JP7.2, X1.32
TIM1_CH2N: JP26.2, X1.33
TIM1_CH2N_OUT: J2.5, JP26.1
TIM1_CH2_LED: JP7.3, R7.2
TIM1_CH2_OUT: J2.4, JP7.1
TIM1_CH3: JP6.2, X1.30
TIM1_CH3N: JP25.2, X1.31
TIM1_CH3N_OUT: J2.3, JP25.1
TIM1_CH3_LED: JP6.3, R6.2
TIM1_CH3_OUT: J2.2, JP6.1
TIM1_CH4: JP5.2, X1.29
TIM1_CH4_LED: JP5.3, R5.2
TIM1_CH4_OUT: J2.1, JP5.1
TIM4_CH1: JP4.2, X1.26
TIM4_CH1_LED: JP4.3, R4.2
TIM4_CH1_OUT: J1.4, JP4.1
TIM4_CH2: JP3.2, X1.25
TIM4_CH2_LED: JP3.3, R3.2
TIM4_CH2_OUT: J1.3, JP3.1
TIM4_CH3: JP2.2, X1.24
TIM4_CH3_LED: JP2.3, R2.2
TIM4_CH3_OUT: J1.2, JP2.1
TIM4_CH4: JP1.2, X1.23
TIM4_CH4_LED: JP1.3, R1.2
TIM4_CH4_OUT: J1.1, JP1.1
UART8_RX: U5.2, X1.5
UART8_TX: U5.3, X1.4
USB_DM: J10.2, X1.20
USB_DP: J10.3, X1.19
USB_ID: J10.4, X1.21

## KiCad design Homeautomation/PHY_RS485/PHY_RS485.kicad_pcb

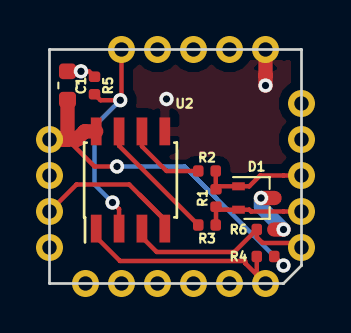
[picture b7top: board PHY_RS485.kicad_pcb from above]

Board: 4 copper layers, 14.0 x 13.0 mm, 10 parts (0 on the bottom side), 10 nets.

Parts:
C1: C; C_0603_1608Metric
D1: SP0502BAJT; SOT-323_SC-70
R1, R2, R3, R4, R5, R6: R; R_0402_1005Metric
U1: LAN8742_INT; LAN8742_INT_B
U2: SN65HVD72DR; SOIC-8_3.9x4.9mm_P1.27mm

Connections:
+3V3: C1.1, R4.1, U1.1, U2.8
CTS: R6.1, U1.11, U2.3
D: U1.3, U2.4
GND: C1.2, D1.3, R5.2, R6.2, U1.16, U2.5
unnamed: D1.1, R1.1, R2.2, U1.13
unnamed: D1.2, R1.2, R3.2, U1.12
unnamed: R2.1, U2.6
unnamed: R3.1, U2.7
R: R4.2, U1.10, U2.1
RTS: R5.1, U1.20, U2.2
